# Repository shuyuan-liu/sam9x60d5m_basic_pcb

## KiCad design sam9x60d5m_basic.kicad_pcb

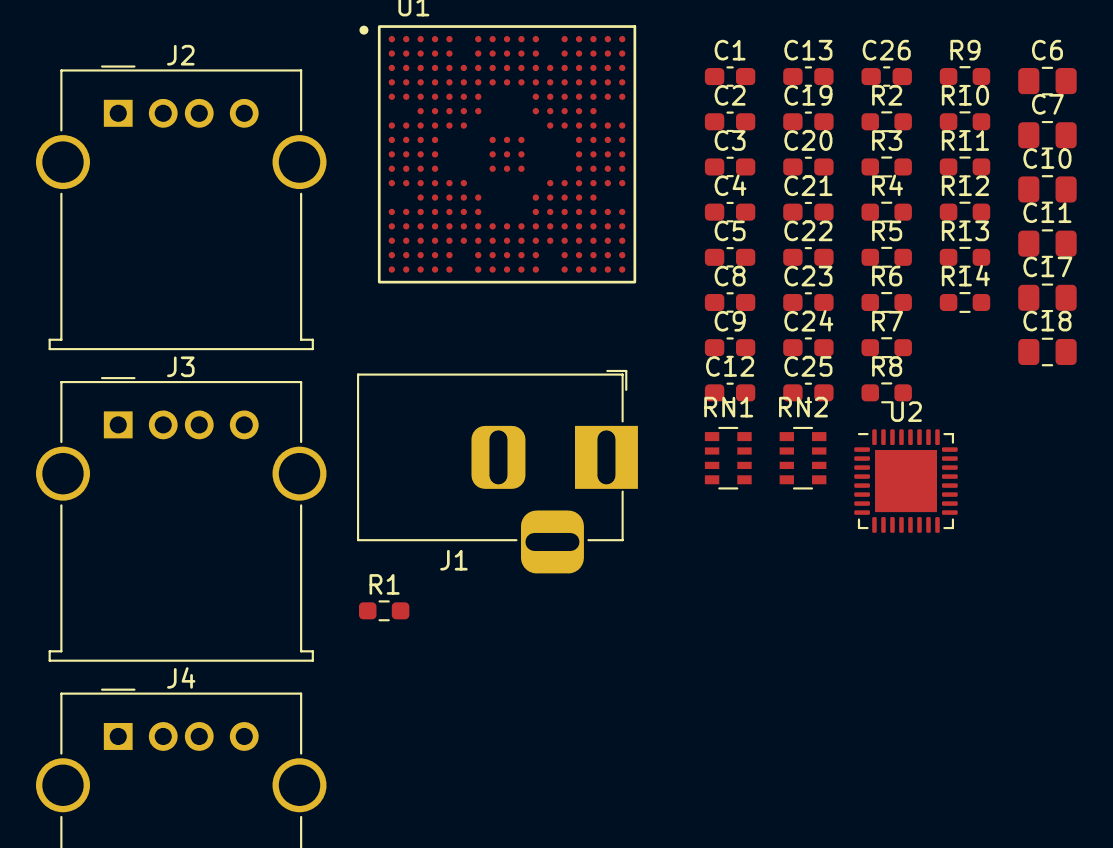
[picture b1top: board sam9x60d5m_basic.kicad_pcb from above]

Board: 4 copper layers, 45 parts (0 on the bottom side), 41 nets, no tracks yet.

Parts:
C1, C9, C13: 47n; C_0603_1608Metric_Pad1.08x0.95mm_HandSolder
C2, C25: 1u; C_0603_1608Metric_Pad1.08x0.95mm_HandSolder
C3, C4, C5: 10u; C_0603_1608Metric_Pad1.08x0.95mm_HandSolder
C6, C7, C10, C11, C17, C18: 22u; C_0805_2012Metric_Pad1.18x1.45mm_HandSolder
C8, C12, C26: 22p; C_0603_1608Metric_Pad1.08x0.95mm_HandSolder
C19: 680p; C_0603_1608Metric_Pad1.08x0.95mm_HandSolder
C20: 1n; C_0603_1608Metric_Pad1.08x0.95mm_HandSolder
C21: 1n8; C_0603_1608Metric_Pad1.08x0.95mm_HandSolder
C22, C23, C24: 10n; C_0603_1608Metric_Pad1.08x0.95mm_HandSolder
J1: Barrel_Jack_Switch; BarrelJack_Horizontal
J2, J3, J4: USB_A; USB_A_Molex_67643_Horizontal
R1: 5k62 ±1%; R_0603_1608Metric_Pad0.98x0.95mm_HandSolder
R2: 27k; R_0603_1608Metric_Pad0.98x0.95mm_HandSolder
R3, R6: 39k; R_0603_1608Metric_Pad0.98x0.95mm_HandSolder
R4: 8k67; R_0603_1608Metric_Pad0.98x0.95mm_HandSolder
R5: 10k; R_0603_1608Metric_Pad0.98x0.95mm_HandSolder
R7: 19k5; R_0603_1608Metric_Pad0.98x0.95mm_HandSolder
R8, R13: 56k; R_0603_1608Metric_Pad0.98x0.95mm_HandSolder
R9: 33k; R_0603_1608Metric_Pad0.98x0.95mm_HandSolder
R10: 18k; R_0603_1608Metric_Pad0.98x0.95mm_HandSolder
R11, R12: 20k; R_0603_1608Metric_Pad0.98x0.95mm_HandSolder
R14: 100k; R_0603_1608Metric_Pad0.98x0.95mm_HandSolder
RN1: 22k; R_Array_Convex_4x0603
RN2: 10k; R_Array_Convex_4x0603
U1: SAM9X60D; BGA-233_14x14mm_Layout17x17_P0.8mm_Ball0.4mm
U2: TPS65261; QFN-32-1EP_5x5mm_P0.5mm_EP3.45x3.45mm

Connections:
+1V8: U1.A16 (DDRM_VDD), U1.B15 (DDRM_VDD), U1.B17 (DDRM_VDD), U1.C14 (DDRM_VDD), U1.C16 (DDRM_VDD), U1.D11 (VDDIOM), U1.D13 (DDRM_VDD), U1.D15 (DDRM_VDD), U1.E11 (DDRM_VDD), U1.E12 (DDRM_VDD), U1.E14 (VDDIOM), U1.F13 (DDRM_VDD), U1.G13 (DDRM_VDD), U1.G14 (VDDIOM)
+1V15: U1.D6 (VDDCORE), U1.D8 (VDDCORE), U1.G5 (VDDCORE), U1.L6 (VDDCORE), U1.M7 (VDDCORE)
+3V3: U1.C6 (VDDQSPI), U1.F5 (VDDIOP0), U1.K4 (VDDIOP0), U1.L4 (VDDIOP0), U1.M3 (VDDIOP1), U1.M15 (VDDNF), U1.N11 (VDDIN33), U1.R6 (VDDBU), U1.R12 (VDDIN33)
/Power/1V8_OUT: C10.2, C11.2, C12.2, R6.2
/Power/1V15_OUT: C17.2, C18.2, C26.2, R11.2
/Power/3V3_OUT: C6.2, C7.2, C8.2, R3.2, R14.1
/Power/POWER_IN: C2.1, C3.1, C4.1, C5.1, R2.1, RN1.5 (R4.2), RN1.6 (R3.2), RN1.7 (R2.2), RN1.8 (R1.2), U2.12 (PVIN2), U2.13 (PVIN3), U2.28 (PVIN1), U2.29 (VIN)
/Power/RESET_OUT: R14.2, U2.2 (PGOOD), U2.3 (RESET)
GND: C2.2, C3.2, C4.2, C5.2, C6.1, C7.1, C10.1, C11.1, C17.1, C18.1, C19.2, C20.2, C21.2, C22.2, C23.2, C24.2, C25.2, J1.2, J2.4 (GND), J2.5 (Shield), J3.4 (GND), J3.5 (Shield), J4.4 (GND), J4.5 (Shield), R1.2, R4.1, R5.2, R7.1, R12.1, R13.2, RN2.1 (R1.1), RN2.2 (R2.1), RN2.3 (R3.1), RN2.4 (R4.1), U1.A1 (GND), U1.A13 (GND), U1.A15 (GND), U1.A17 (DDRM_VSS), U1.B2 (GND), U1.B13 (GND), U1.B14 (GND), U1.B16 (DDRM_VSS), U1.C3 (GNDANA), U1.C9 (GND), U1.C12 (DDRM_VSS), U1.C13 (GND), U1.C15 (DDRM_VSS), U1.D4 (GND), U1.D14 (DDRM_VSS), U1.E5 (GND), U1.E6 (GND), U1.E7 (GND), U1.E13 (DDRM_VSS), U1.F3 (GND), U1.F6 (GND), U1.F7 (GND), U1.F11 (DDRM_VSS), U1.F12 (DDRM_VSS), U1.F15 (DDRM_VSS), U1.G6 (GND), U1.G12 (DDRM_VSS), U1.H8 (GND), U1.H9 (GND), U1.H10 (GND), U1.J3 (GND), U1.J8 (GND), U1.J9 (GND), U1.J10 (GND), U1.J15 (GND), U1.K8 (GND), U1.K9 (GND), U1.K10 (GND), U1.L5 (GND), U1.L12 (GND), U1.L13 (GND), U1.L14 (GND), U1.M5 (GND), U1.M6 (GND), U1.M11 (GND), U1.M12 (GND), U1.M13 (GND), U1.M14 (GND), U1.N5 (GND), U1.N6 (GND), U1.N7 (GNDIN33), U1.N12 (GND), U1.N13 (GND), U1.P4 (GND), U1.P7 (GNDIN33), U1.P10 (GND), U1.P14 (GND), U1.R3 (GND), U1.R9 (GND), U1.R11 (GND), U1.R15 (GND), U1.R16 (GND), U1.T2 (GND), U1.T16 (GND), U1.U1 (GND), U1.U15 (GND), U1.U17 (GND), U2.11 (PGND2), U2.14 (PGND3), U2.21 (AGND), U2.27 (PGND1), U2.33 (PAD)
unnamed: C19.1, R8.2
unnamed: C20.1, R9.2
unnamed: C21.1, R10.2
unnamed: RN1.1 (R1.1), RN2.8 (R1.2), U2.1 (EN3)
unnamed: RN1.2 (R2.1), RN2.7 (R2.2), U2.32 (EN2)
unnamed: RN1.3 (R3.1), RN2.6 (R3.2), U2.31 (EN1)
unnamed: RN1.4 (R4.1), RN2.5 (R4.2), U2.4 (MODE)
unnamed: C1.1, U2.25 (BST1)
unnamed: C9.1, U2.9 (BST2)
unnamed: C13.1, U2.16 (BST3)
unnamed: R8.1, U2.23 (COMP1)
unnamed: R9.1, U2.7 (COMP2)
unnamed: R10.1, U2.18 (COMP3)
unnamed: C8.1, R3.1, R4.2, U2.22 (FB1)
unnamed: C12.1, R6.1, R7.2, U2.6 (FB2)
unnamed: C26.1, R11.1, R12.2, U2.19 (FB3)
unnamed: C1.2, U2.26 (LX1)
unnamed: C9.2, U2.10 (LX2)
unnamed: C13.2, U2.15 (LX3)
unnamed: R13.1, U2.20 (ROSC)
unnamed: C22.1, U2.24 (SS1)
unnamed: C23.1, U2.8 (SS2)
unnamed: C24.1, U2.17 (SS3)
unnamed: C25.1, U2.5 (V7V)
unnamed: R2.2, R5.1, U2.30 (VDIV)
USBA_D+: J2.2 (D-), U1.T15 (HHSDPA)
USBA_D-: J2.3 (D+), U1.U16 (HHSDMA)
USBB_D+: J3.3 (D+), U1.T17 (HHSDPB)
USBB_D-: J3.2 (D-), U1.R17 (HHSDMB)
USBC_D+: J4.3 (D+), U1.P16 (HHSDPC)
USBC_D-: J4.2 (D-), U1.P15 (HHSDMC)
USB_RTUNE: R1.1, U1.P17 (RTUNE)

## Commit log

2023-10-11 Create repo; add existing schematic and PCB
2023-10-11 Add kipart-compatible pin assignment file for the SAM9X60D
2023-10-11 Update filename references in documents to follow project name change
2023-10-26 Finish buck converters; include custom symbols and footprints
2023-10-26 Add .gitignore to exclude backup and cache files
